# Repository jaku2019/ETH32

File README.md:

# Supla powered ETH32 light coontroller
Thanks to the amazing help of @elmaya @radzik_r @klew and othher forum.supla.org users I managed to create ETH32 light controller.

## Main characteristics
- 17 230V inputs (in the photo sample: 16x230V 1x12V) [PC814]
- 18 230V 5A inputs [HF46F/12V]
- TEST button that turns on all the relays (you can change that function in the code)
- LAN8721
- 2xMCP23017 (there is a possibility to channge its addresses with DIN switches)
- easy-access pins: 3,3V, 5V, GND, IO12, IO15, IO35, IO36, IO39, IO0, RX, TX
- easy access to I2C pins
- MCP9808 temperature sensor (there is a possibility to channge its address with DIN switch)
- RTC clock DS3231
- FRAM memory MB85RC256V (there is a possibility to channge its address with DIN switch)

## Info
Instead of soldering the buck converter elements to the PCB, you can insert a ready module LM2596 (it is necessary to set its output voltage to 5V)

ESP is connected with IO by MCP23017. One of this modules was placed on a card that is a bit loose. You shouldn't play with it when ETH32 is on, as it could make the relays stop working. Repositioning it to 90 degrees should solve the problem.

The PCB is designed to fit perfectly in the Kradex ZD1012 enclosure for DIN rail.
## The code
In the software example relays no. 101-116 have assigned inputs with relative numbers. 

Input no. 117 turns on all the relays.
Single click = turn on (all),
double click = turn off (all). 

Everything is preperad to work with monostable buttons. 

There is no thermometer, FRAM memory nor RTC support yet.
## Smart home control
You need to set your Supla accunt mail and server address in the coode (relative fields are placed in the bottom of the code).

You can integrate Supla with e.g. Home Assistant via MQTT. The setup is pretty easy and reliable. https://en-forum.supla.org/viewtopic.php?t=10419

## On the din rail
And that's how it ended! 

You can download a Word file, where you can find ready labels to stick on the enclosure.

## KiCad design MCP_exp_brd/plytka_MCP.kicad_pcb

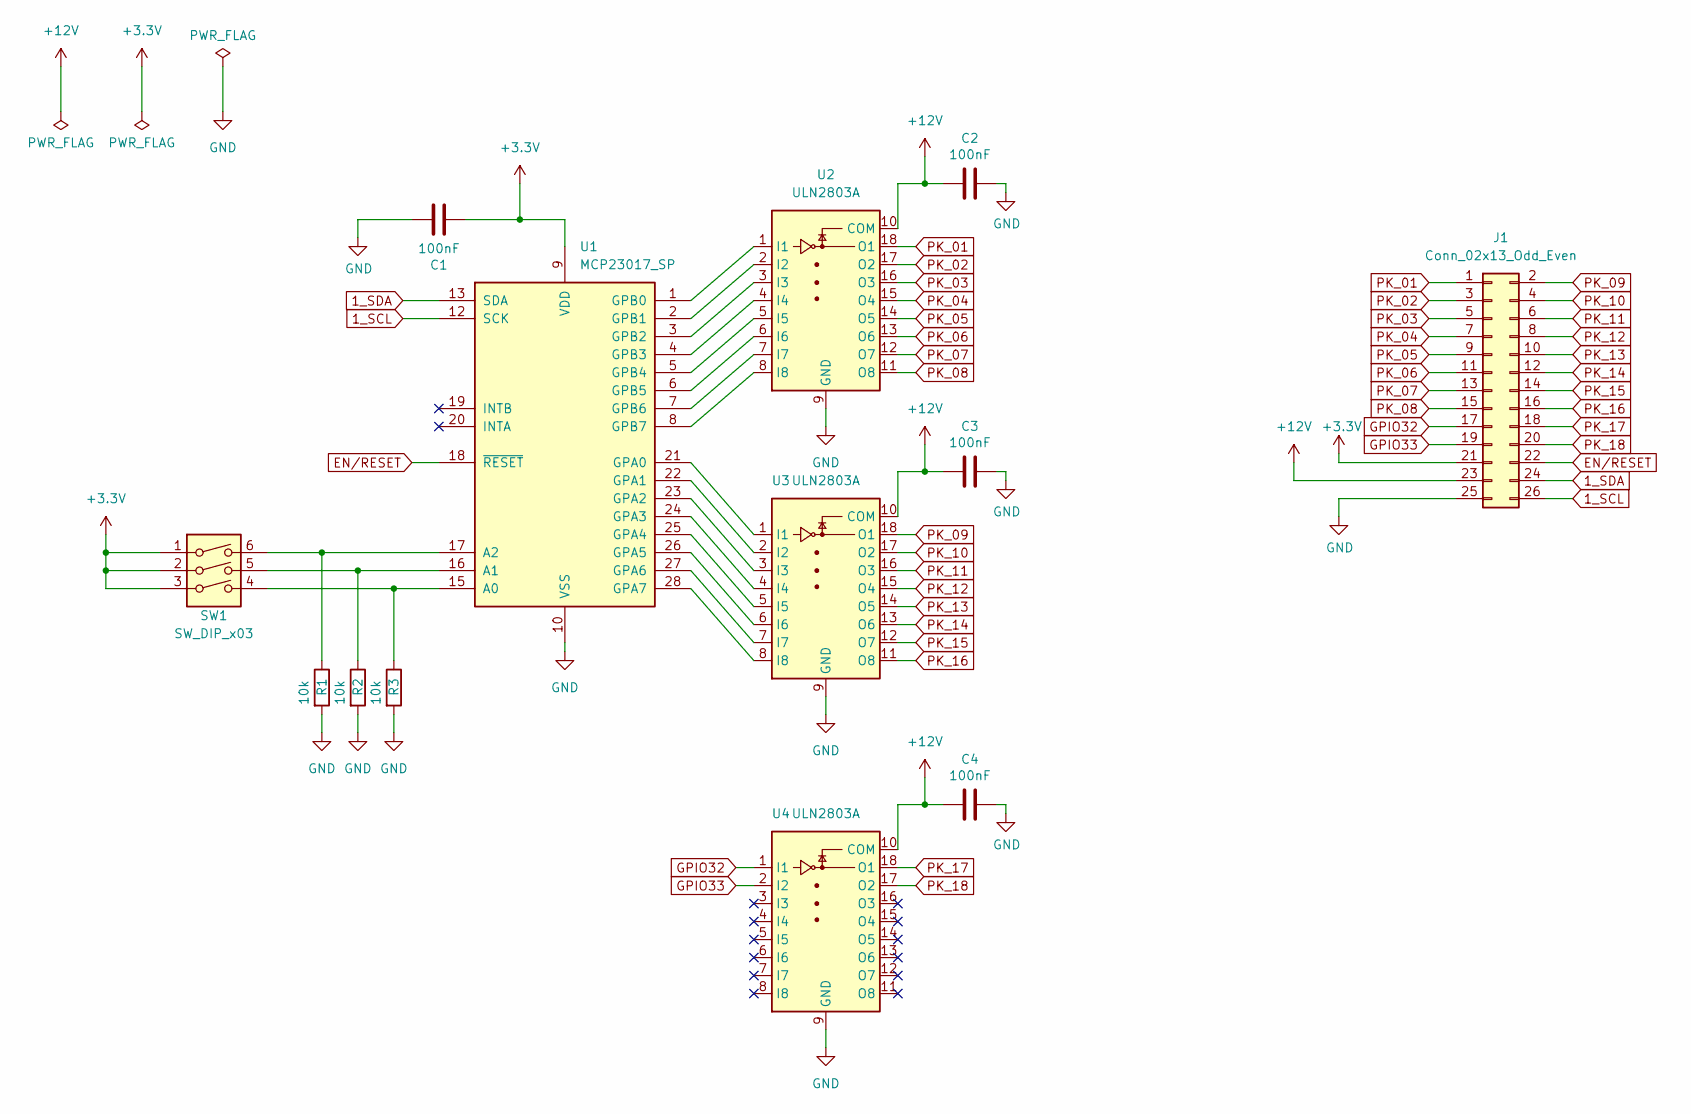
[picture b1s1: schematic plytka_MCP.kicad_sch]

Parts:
C1, C2, C3, C4: 100nF; C_0603_1608Metric; JLCPCB C14663
J1: Conn_02x13_Odd_Even; PinHeader_2x13_P2.00mm_Horizontal; JLCPCB C2883270
R1, R2, R3: 10k; R_0603_1608Metric; JLCPCB C238881
SW1: SW_DIP_x03; SW_DIP_SPSTx03_Slide_KingTek_DSHP03TS_W7.62mm_P1.27mm; JLCPCB C319051
U1: MCP23017_SP; DIP-28_W7.62mm_Socket; JLCPCB C16653
U2, U3, U4: ULN2803A; SOIC-18W_7.5x11.6mm_P1.27mm; JLCPCB C845537

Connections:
1_SCL: J1.26, U1.12 (SCK)
1_SDA: J1.24, U1.13 (SDA)
+3V3: C1.2, J1.21, SW1.1, SW1.2, SW1.3, U1.9 (VDD)
+12V: C2.2, C3.2, C4.2, J1.23, U2.10 (COM), U3.10 (COM), U4.10 (COM)
EN/RESET: J1.22, U1.18 (~RESET)
GND: C1.1, C2.1, C3.1, C4.1, J1.25, R1.2, R2.2, R3.2, U1.10 (VSS), U2.9 (GND), U3.9 (GND), U4.9 (GND)
GPIO32: J1.17, U4.1 (I1)
GPIO33: J1.19, U4.2 (I2)
unnamed: R1.1, SW1.6, U1.17 (A2)
unnamed: R2.1, SW1.5, U1.16 (A1)
unnamed: R3.1, SW1.4, U1.15 (A0)
unnamed: U1.1 (GPB0), U2.1 (I1)
unnamed: U1.2 (GPB1), U2.2 (I2)
unnamed: U1.3 (GPB2), U2.3 (I3)
unnamed: U1.4 (GPB3), U2.4 (I4)
unnamed: U1.5 (GPB4), U2.5 (I5)
unnamed: U1.6 (GPB5), U2.6 (I6)
unnamed: U1.7 (GPB6), U2.7 (I7)
unnamed: U1.8 (GPB7), U2.8 (I8)
unnamed: U1.21 (GPA0), U3.1 (I1)
unnamed: U1.22 (GPA1), U3.2 (I2)
unnamed: U1.23 (GPA2), U3.3 (I3)
unnamed: U1.24 (GPA3), U3.4 (I4)
unnamed: U1.25 (GPA4), U3.5 (I5)
unnamed: U1.26 (GPA5), U3.6 (I6)
unnamed: U1.27 (GPA6), U3.7 (I7)
unnamed: U1.28 (GPA7), U3.8 (I8)
PK_01: J1.1, U2.18 (O1)
PK_02: J1.3, U2.17 (O2)
PK_03: J1.5, U2.16 (O3)
PK_04: J1.7, U2.15 (O4)
PK_05: J1.9, U2.14 (O5)
PK_06: J1.11, U2.13 (O6)
PK_07: J1.13, U2.12 (O7)
PK_08: J1.15, U2.11 (O8)
PK_09: J1.2, U3.18 (O1)
PK_10: J1.4, U3.17 (O2)
PK_11: J1.6, U3.16 (O3)
PK_12: J1.8, U3.15 (O4)
PK_13: J1.10, U3.14 (O5)
PK_14: J1.12, U3.13 (O6)
PK_15: J1.14, U3.12 (O7)
PK_16: J1.16, U3.11 (O8)
PK_17: J1.18, U4.18 (O1)
PK_18: J1.20, U4.17 (O2)

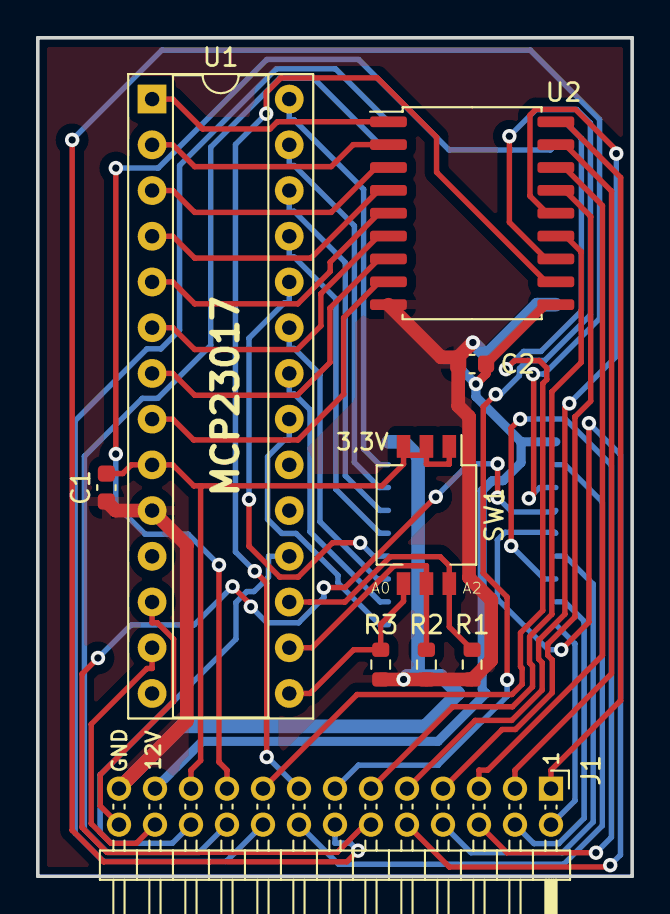
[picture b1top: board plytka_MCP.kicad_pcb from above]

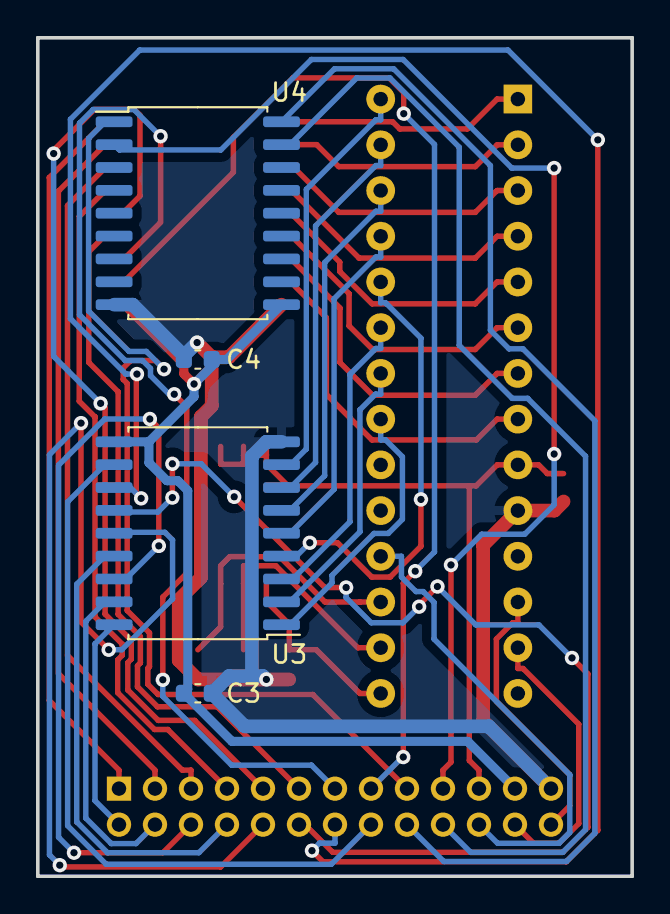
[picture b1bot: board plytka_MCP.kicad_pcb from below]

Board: 2 copper layers, 33.0 x 46.6 mm, 13 parts (4 on the bottom side), 45 nets.

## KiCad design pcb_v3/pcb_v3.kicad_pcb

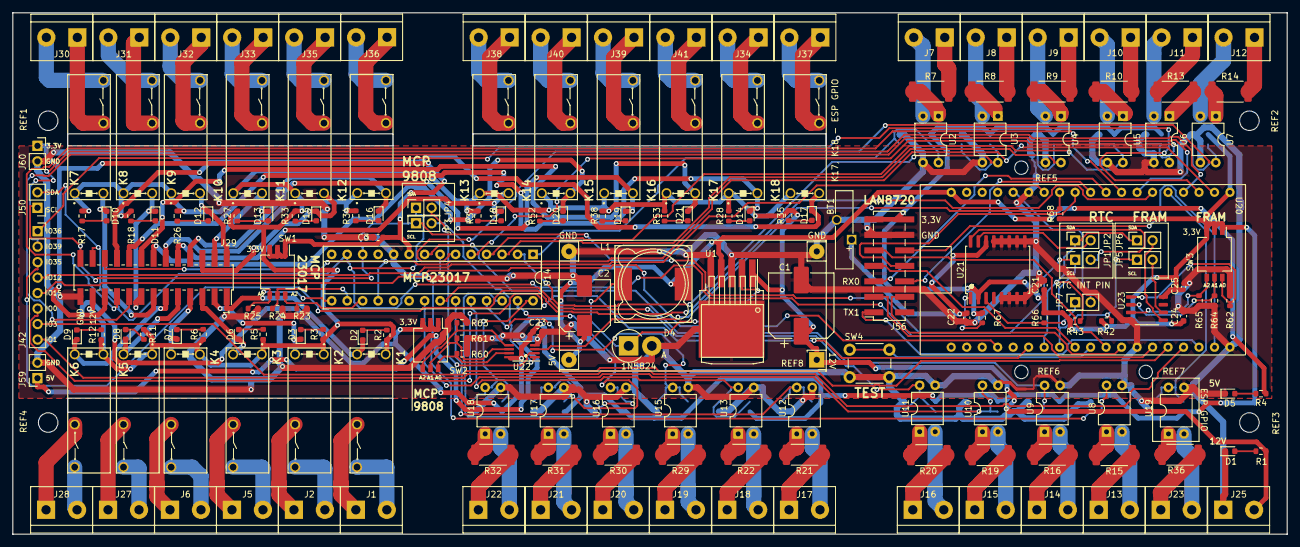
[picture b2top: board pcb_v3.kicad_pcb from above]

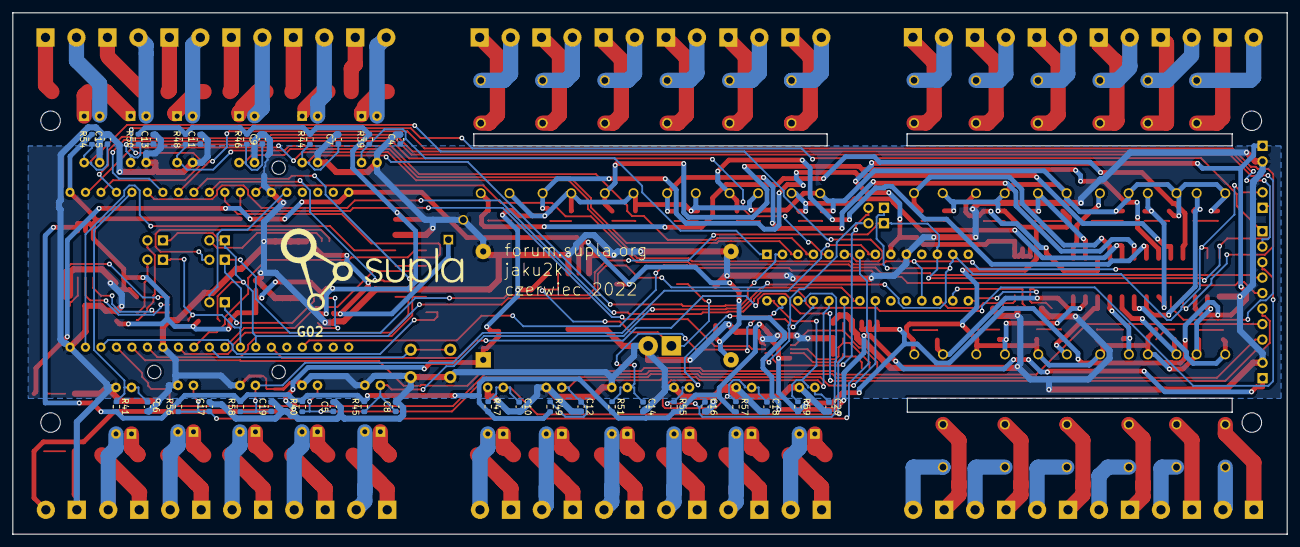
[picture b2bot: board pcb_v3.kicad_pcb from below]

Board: 2 copper layers, 209.0 x 85.5 mm, 219 parts (35 on the bottom side), 190 nets.

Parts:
BT1: Battery; Battery_Panasonic_CR1220-VCN_Vertical_CircularHoles
C1: C_Polarized 680μF; CP_Elec_10x10.5
C2: C_Polarized 220μF; CP_Elec_8x10
C3, C4, C5, C6, C7, C8, C9, C10, C11, C12, C13, C14, C15, C16, C17, C18, C19, C20, C21, C22, C23, C24: 100nF; C_0603_1608Metric
C25: 10nF; C_0402_1005Metric
D1, D2, D3, D5, D6, D7, D8, D9, D10, D11, D12, D13, D14, D15, D16, D17, D18, D19, D20, D21: D_Photo; LED_0603_1608Metric
D4: 1N5824; D_DO-201AD_P3.81mm_Vertical_AnodeUp
G02: LOGO; supla_logo_3cm
J1, J2, J5, J6, J7, J8, J9, J10, J11, J12, J13, J14, J15, J16, J17, J18, J19, J20, J21, J22, J23, J25, J27, J28, J30, J31, J32, J33, J34, J35, J36, J37, J38, J39, J40, J41: Screw_Terminal_01x02; TerminalBlock_bornier-2_P5.08mm
J29: Conn_02x13_Odd_Even; PinSocket_2x13_P2.00mm_Vertical_SMD
J42: Conn_01x08_Female; PinSocket_1x08_P2.54mm_Vertical
J50: Conn_01x02_Male; PinHeader_1x02_P2.54mm_Vertical
J56: PinHeader_2x07_P2.54mm_Vertical_SMD
J59, J60: Conn_01x02_Male; PinSocket_1x02_P2.54mm_Vertical
JP1, JP2, JP3, JP4, JP5, JP6, JP7: SolderJumper_2_Open; PinHeader_2x01_P2.54mm_Vertical
K1, K2, K3, K4, K5, K6, K7, K8, K9, K10, K11, K12, K13, K14, K15, K16, K17, K18: HF46F/12V; HF46F
L1: 33μH; L_12x12mm_H8mm
R1, R2, R3, R5, R6, R11, R12, R17, R18, R26, R27, R28, R33, R34, R35, R37, R38, R52, R53: 2k; R_0603_1608Metric
R4: 600k; R_0603_1608Metric
R7, R8, R9, R10, R13, R14, R15, R16, R19, R20, R21, R22, R29, R30, R31, R32, R36: 47k; R_2512_6332Metric
R23, R24, R25, R39, R40, R41, R44, R45, R46, R47, R48, R49, R50, R51, R54, R55, R56, R57, R58, R59, R60, R61, R62, R63, R64, R65, R68: 10k; R_0603_1608Metric
R42, R43, R66, R67: 4,7k; R_0603_1608Metric
REF1, REF2, REF3, REF4: MountingHole_3.2mm_M3
REF5, REF6, REF7: MountingHole_2.2mm_M2_ISO14580
REF8: YAAJ_DCDC_StepDown_LM2596
SW1, SW2, SW3: SW_DIP_x03; SW_DIP_SPSTx03_Slide_KingTek_DSHP03TS_W7.62mm_P1.27mm
SW4: SW_Push (TEST); SW_PUSH_6mm_H5mm
U1: LM2596T-5; TO-263-5_TabPin3
U2, U3, U4, U5, U6, U7, U8, U9, U10, U11, U12, U13, U15, U16, U17, U18, U19: LTV-814; DIP-4_W7.62mm
U14: MCP23017_SP; DIP-28_W7.62mm_Socket
U20: ESP32_38pin
U21: DS3231M; SOIC-16W_7.5x10.3mm_P1.27mm
U22: MCP9808_MSOP; MSOP-8_3x3mm_P0.65mm
U23: MB85RC256V; SSOP-8_3.9x5.05mm_P1.27mm

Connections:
1_SCL: J29.26, J50.1, JP1.1 (A), JP3.1 (A), JP5.1 (A), R42.1, U14.12 (SCK), U20.31 (GPIO16)
1_SDA: J29.24, J50.2, JP2.1 (A), JP4.1 (A), JP6.1 (A), R43.1, U14.13 (SDA), U20.32 (GPIO04)
+3V3: C3.2, C21.1, C23.2, C24.1, C25.1, J29.21, J56.13, J56.14, J60.1, R39.2, R40.2, R41.2, R42.2, R43.2, R44.2, R45.2, R46.2, R47.2, R48.2, R49.2, R50.2, R51.2, R54.2, R55.2, R56.2, R57.2, R58.2, R59.2, R66.2, R67.2, R68.2, SW1.1, SW1.2, SW1.3, SW2.1, SW2.2, SW2.3, SW3.1, SW3.2, SW3.3, U14.9 (VDD), U20.1 (3,3V), U21.2 (VCC), U22.8 (VDD), U23.8 (VCC)
+5V: C2.1, J59.1, L1.2, R4.1, REF8.4, U1.4 (FB), U20.19 (5V)
+12V: C1.1, J25.2, J29.23, K1.1, K2.1, K3.1, K4.1, K5.1, K6.1, K7.1, K8.1, K9.1, K10.1, K11.1, K12.1, K13.1, K14.1, K15.1, K16.1, K17.1, K18.1, R1.1, R2.1, R3.1, R5.1, R6.1, R11.1, R12.1, R17.1, R18.1, R26.1, R27.1, R28.1, R33.1, R34.1, R35.1, R37.1, R38.1, R52.1, R53.1, REF8.1, U1.1 (VIN)
EN/RESET: J29.22, U14.18 (~RESET), U20.2 (EN/RESET)
GND: BT1.2 (-), C1.2, C2.2, C3.1, C4.2, C5.2, C6.2, C7.2, C8.2, C9.2, C10.2, C11.2, C12.2, C13.2, C14.2, C15.2, C16.2, C17.2, C18.2, C19.2, C20.2, C21.2, C22.2, C23.1, C24.2, C25.2, D1.1 (K), D4.2 (A), D5.1 (K), J25.1, J29.25, J56.11, J56.12, J59.2, J60.2, R23.2, R24.2, R25.2, R60.2, R61.2, R62.2, R63.2, R64.2, R65.2, REF8.2, REF8.3, SW4.1, U1.3 (GND), U1.5 (~ON/OFF), U2.3, U3.3, U4.3, U5.3, U6.3, U7.3, U8.3, U9.3, U10.3, U11.3, U12.3, U13.3, U14.10 (VSS), U15.3, U16.3, U17.3, U18.3, U19.3, U20.14 (GND), U20.20 (GND), U20.26 (GND), U21.5 (GND), U21.6 (GND), U21.7 (GND), U21.8 (GND), U21.9 (GND), U21.10 (GND), U21.11 (GND), U21.12 (GND), U21.13 (GND), U22.4 (GND), U23.4 (GND)
GPIO0: J42.6, U20.33 (GPIO0)
GPIO01/TX0: J42.8, U20.23 (GPIO01/TX0)
GPIO03/RX0: J42.7, U20.24 (GPIO03/RX0)
GPIO12: J42.4, U20.13 (GPIO12)
GPIO15: J42.5, U20.35 (GPIO15)
GPIO32: J29.17, U20.7 (GPIO32)
GPIO33: J29.19, U20.8 (GPIO33)
GPIO34: C6.1, R41.1, U19.4, U20.5 (GPIO34)
GPIO35: J42.3, U20.6 (GPIO35)
GPIO36: J42.1, U20.3 (GPIO36)
GPIO39: J42.2, U20.4 (GPIO39)
LAN 8720 CRS: J56.8, U20.11 (GPIO27)
LAN 8720 MDC: J56.10, U20.21 (GPIO23)
LAN 8720 MDIO: J56.9, U20.28 (GPIO18)
LAN 8720 RX0: J56.5, U20.9 (GPIO25)
LAN 8720 RX1: J56.6, U20.10 (GPIO26)
LAN 8720 TX0: J56.4, U20.27 (GPIO19)
LAN 8720 TX1: J56.1, U20.22 (GPIO22)
LAN 8720 TX_EN: J56.3, U20.25 (GPIO21)
LAN 8720 nINT/REFCLK: J56.7, U20.30 (GPIO17)
N1: J7.2, U2.2
N2: J8.2, U3.2
N3: J9.2, U4.2
N4: J10.2, U5.2
N5: J11.2, U6.2
N6: J12.2, U7.2
N7: J13.2, U8.2
N8: J14.2, U9.2
N9: J15.2, U10.2
N10: J16.2, U11.2
N11: J17.2, U12.2
N12: J18.2, U13.2
N13: J19.2, U15.2
N14: J20.2, U16.2
N15: J21.2, U17.2
N16: J22.2, U18.2
N17: J23.2, U19.2
unnamed: BT1.1 (+), C22.1, U21.14 (VBAT)
unnamed: D1.2 (A), R1.2
unnamed: D2.2 (A), R2.2
unnamed: D3.2 (A), R3.2
unnamed: D4.1 (K), L1.1, U1.2 (OUT)
unnamed: D5.2 (A), R4.2
unnamed: D6.2 (A), R5.2
unnamed: D7.2 (A), R6.2
unnamed: D8.2 (A), R11.2
unnamed: D9.2 (A), R12.2
unnamed: D10.2 (A), R17.2
unnamed: D11.2 (A), R18.2
unnamed: D12.2 (A), R26.2
unnamed: D13.2 (A), R27.2
unnamed: D14.2 (A), R28.2
unnamed: D15.2 (A), R33.2
unnamed: D16.2 (A), R34.2
unnamed: D17.2 (A), R35.2
unnamed: D18.2 (A), R37.2
unnamed: D19.2 (A), R38.2
unnamed: D20.2 (A), R52.2
unnamed: D21.2 (A), R53.2
unnamed: J1.1, K1.3
unnamed: J1.2, K1.4
unnamed: J2.1, K2.3
unnamed: J2.2, K2.4
unnamed: J5.1, K3.3
unnamed: J5.2, K3.4
unnamed: J6.1, K4.3
unnamed: J6.2, K4.4
unnamed: J27.1, K5.3
unnamed: J27.2, K5.4
unnamed: J28.1, K6.3
unnamed: J28.2, K6.4
unnamed: J30.1, K7.3
unnamed: J30.2, K7.4
unnamed: J31.1, K8.3
unnamed: J31.2, K8.4
unnamed: J32.1, K9.3
unnamed: J32.2, K9.4
unnamed: J33.1, K10.3
unnamed: J33.2, K10.4
unnamed: J34.1, K17.3
unnamed: J34.2, K17.4
unnamed: J35.1, K11.3
unnamed: J35.2, K11.4
unnamed: J36.1, K12.3
unnamed: J36.2, K12.4
unnamed: J37.1, K18.3
unnamed: J37.2, K18.4
unnamed: J38.1, K13.3
unnamed: J38.2, K13.4
unnamed: J39.1, K15.3
unnamed: J39.2, K15.4
unnamed: J40.1, K14.3
unnamed: J40.2, K14.4
unnamed: J41.1, K16.3
unnamed: J41.2, K16.4
unnamed: JP1.2 (B), U21.16 (SCL)
unnamed: JP2.2 (B), U21.15 (SDA)
unnamed: JP3.2 (B), U22.1 (SDA)
unnamed: JP4.2 (B), U22.2 (SCL)
unnamed: JP5.2 (B), U23.6 (SCL)
unnamed: JP6.2 (B), U23.5 (SDA)
unnamed: JP7.1 (A), R66.1, U21.3 (~INT/SQW)
unnamed: R7.2, U2.1
unnamed: R8.2, U3.1
unnamed: R9.2, U4.1
unnamed: R10.2, U5.1
unnamed: R13.2, U6.1
unnamed: R14.2, U7.1
unnamed: R15.2, U8.1
unnamed: R16.2, U9.1
unnamed: R19.2, U10.1
unnamed: R20.2, U11.1
unnamed: R21.2, U12.1
unnamed: R22.2, U13.1
unnamed: R23.1, SW1.6, U14.17 (A2)
unnamed: R24.1, SW1.5, U14.16 (A1)
unnamed: R25.1, SW1.4, U14.15 (A0)
unnamed: R29.2, U15.1
unnamed: R30.2, U16.1
unnamed: R31.2, U17.1
unnamed: R32.2, U18.1
unnamed: R36.2, U19.1
unnamed: R60.1, SW2.6, U22.7 (A0)
unnamed: R61.1, SW2.5, U22.6 (A1)
unnamed: R62.1, SW3.6, U23.1 (A0)
unnamed: R63.1, SW2.4, U22.5 (A2)
unnamed: R64.1, SW3.5, U23.2 (A1)
unnamed: R65.1, SW3.4, U23.3 (A2)
unnamed: R67.1, U21.1 (32KHZ)
PK_01: D2.1 (K), J29.1, K1.2
PK_02: D3.1 (K), J29.3, K2.2
PK_03: D6.1 (K), J29.5, K3.2
PK_04: D7.1 (K), J29.7, K4.2
PK_05: D8.1 (K), J29.9, K5.2
PK_06: D9.1 (K), J29.11, K6.2
PK_07: D10.1 (K), J29.13, K7.2
PK_08: D11.1 (K), J29.15, K8.2
PK_09: D12.1 (K), J29.2, K9.2
PK_10: D13.1 (K), J29.4, K10.2
PK_11: D15.1 (K), J29.6, K11.2
PK_12: D16.1 (K), J29.8, K12.2
PK_13: D18.1 (K), J29.10, K13.2
PK_14: D19.1 (K), J29.12, K15.2
PK_15: D20.1 (K), J29.14, K14.2
PK_16: D21.1 (K), J29.16, K16.2
PK_17: D14.1 (K), J29.18, K17.2
PK_18: D17.1 (K), J29.20, K18.2
WE01: SW4.2, U20.29 (GPIO05)
WE02: JP7.2 (B), U20.15 (GPIO13)
WE03: R68.1, U20.12 (GPIO14), U22.3 (Alert)
WEAC_01: J7.1, R7.1
WEAC_02: J8.1, R8.1
WEAC_03: J9.1, R9.1
WEAC_04: J10.1, R10.1
WEAC_05: J11.1, R13.1
WEAC_06: J12.1, R14.1
WEAC_07: J13.1, R15.1
WEAC_08: J14.1, R16.1
WEAC_09: J15.1, R19.1
WEAC_10: J16.1, R20.1
WEAC_11: J17.1, R21.1
WEAC_12: J18.1, R22.1
WEAC_13: J19.1, R29.1
WEAC_14: J20.1, R30.1
WEAC_15: J21.1, R31.1
WEAC_16: J22.1, R32.1
WEAC_17: J23.1, R36.1
WE_01: C4.1, R39.1, U2.4, U14.1 (GPB0)
WE_02: C7.1, R44.1, U3.4, U14.2 (GPB1)
WE_03: C9.1, R46.1, U4.4, U14.3 (GPB2)
WE_04: C11.1, R48.1, U5.4, U14.4 (GPB3)
WE_05: C13.1, R50.1, U6.4, U14.5 (GPB4)
WE_06: C15.1, R54.1, U7.4, U14.6 (GPB5)
WE_07: C17.1, R56.1, U8.4, U14.7 (GPB6)
WE_08: C19.1, R58.1, U9.4, U14.8 (GPB7)
WE_09: C5.1, R40.1, U10.4, U14.21 (GPA0)
WE_10: C8.1, R45.1, U11.4, U14.22 (GPA1)
WE_11: C10.1, R47.1, U12.4, U14.23 (GPA2)
WE_12: C12.1, R49.1, U13.4, U14.24 (GPA3)
WE_13: C14.1, R51.1, U14.25 (GPA4), U15.4
WE_14: C16.1, R55.1, U14.26 (GPA5), U16.4
WE_15: C18.1, R57.1, U14.27 (GPA6), U17.4
WE_16: C20.1, R59.1, U14.28 (GPA7), U18.4

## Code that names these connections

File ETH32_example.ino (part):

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
/*
-(50MHz) Osc. Enable to GND -
GPIO22 - EMAC_TXD1   : TX1
GPIO19 - EMAC_TXD0   : TX0
GPIO21 - EMAC_TX_EN  : TX_EN
GPIO26 - EMAC_RXD1   : RX1
GPIO25 - EMAC_RXD0   : RX0
GPIO27 - EMAC_RX_DV  : CRS
GPIO17 - EMAC_TX_CLK : nINT/REFCLK (50MHz)
GPIO23 - SMI_MDC     : MDC
GPIO18 - SMI_MDIO    : MDIO
GND                  : GND
3V3                  : VCC
*/
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

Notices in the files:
ETH32_example.ino:
Copyright (C) AC SOFTWARE SP. Z O.O.
modify it under the terms of the GNU General Public License
